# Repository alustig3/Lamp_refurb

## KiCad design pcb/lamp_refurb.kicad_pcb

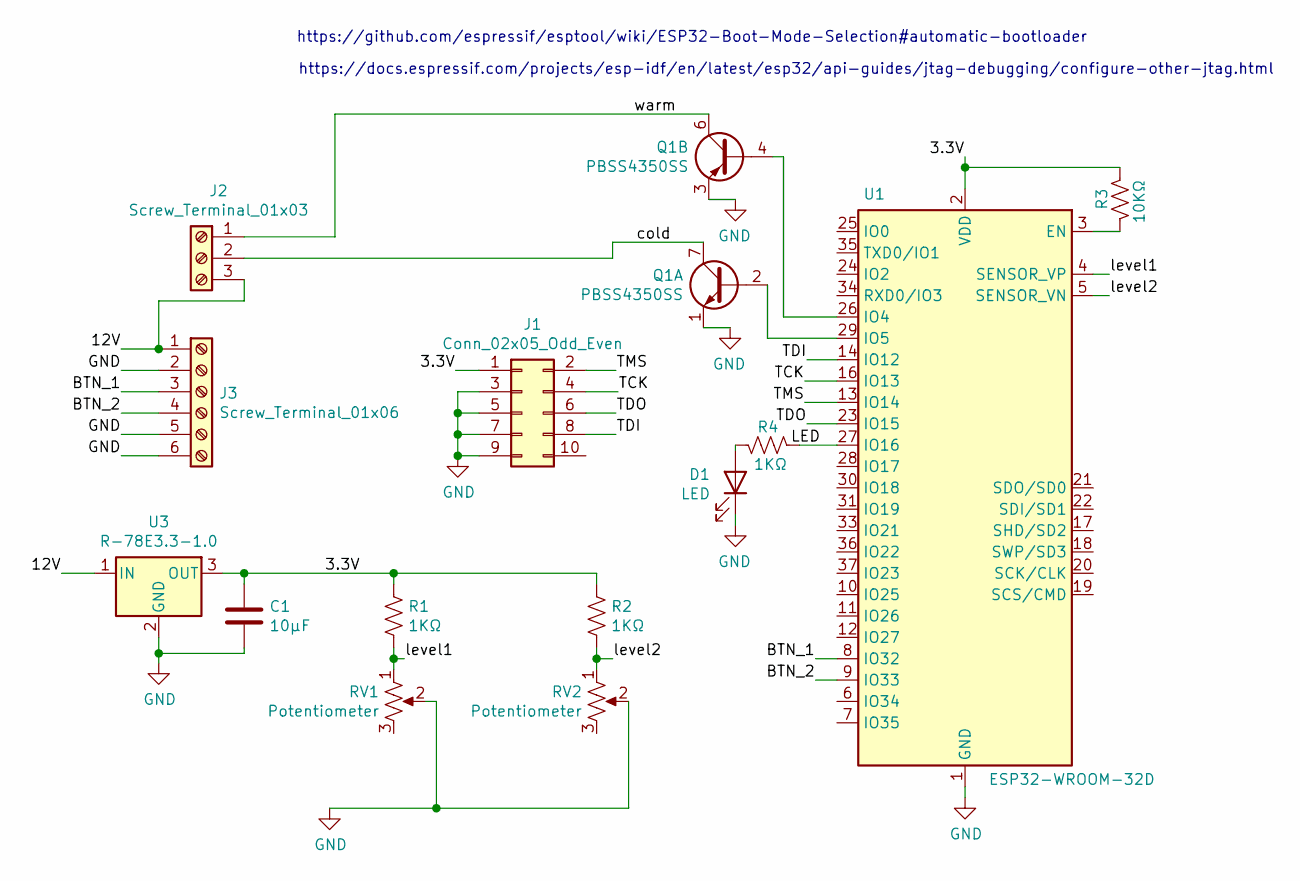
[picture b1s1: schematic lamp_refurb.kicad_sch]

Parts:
C1: 10µF; C_0805_2012Metric
D1: LED; LED_0805_2012Metric
J1: Conn_02x05_Odd_Even; SWD_2x5_socket
J2: Screw_Terminal_01x03; PinHeader_1x03_P2.54mm_Vertical
J3: Screw_Terminal_01x06; PinHeader_1x06_P2.54mm_Vertical
Q1: PBSS4350SS; SOIC-8_3.9x4.9mm_P1.27mm
R1, R2, R4: 1KΩ; R_0805_2012Metric
R3: 10KΩ; R_0805_2012Metric
RV1, RV2: Potentiometer; Panel_mount_pot
U1: ESP32-WROOM-32D; ESP32-WROOM-32
U3: R-78E3.3-1.0; Converter_DCDC_RECOM_R-78E-0.5_THT

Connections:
/3.3V: C1.1, J1.1, R1.1, R2.1, R3.2, U1.2 (VDD), U3.3 (OUT)
/12V: J2.3, J3.1, U3.1 (IN)
/BTN_1: J3.3, U1.8 (IO32)
/BTN_2: J3.4, U1.9 (IO33)
/LED: R4.2, U1.27 (IO16)
/TCK: J1.4, U1.16 (IO13)
/TDI: J1.8, U1.14 (IO12)
/TDO: J1.6, U1.23 (IO15)
/TMS: J1.2, U1.13 (IO14)
/cold: J2.2, Q1.7 (C1)
/level1: R1.2, RV1.1, U1.4 (SENSOR_VP)
/level2: R2.2, RV2.1, U1.5 (SENSOR_VN)
/warm: J2.1, Q1.6 (C2)
GND: C1.2, D1.1 (K), J1.3, J1.5, J1.7, J1.9, J3.2, J3.5, J3.6, Q1.1 (E1), Q1.3 (E2), RV1.2, RV2.2, U1.1 (GND), U1.15 (GND), U1.38 (GND), U1.39 (GND), U3.2 (GND)
unnamed: D1.2 (A), R4.1
unnamed: Q1.2 (B1), U1.29 (IO5)
unnamed: Q1.4 (B2), U1.26 (IO4)
unnamed: R3.1, U1.3 (EN)

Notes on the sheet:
https://github.com/espressif/esptool/wiki/ESP32-Boot-Mode-Selection#automatic-bootloader
https://docs.espressif.com/projects/esp-idf/en/latest/esp32/api-guides/jtag-debugging/configure-other-jtag.html

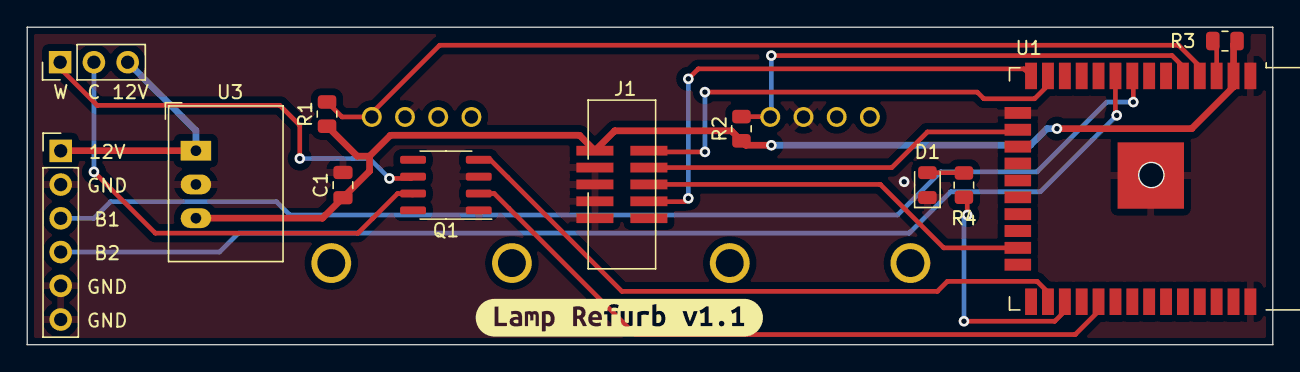
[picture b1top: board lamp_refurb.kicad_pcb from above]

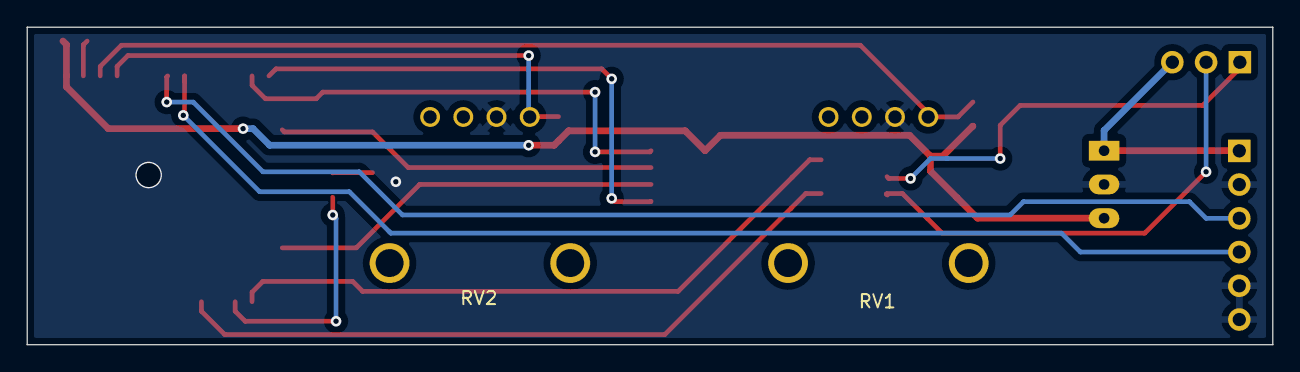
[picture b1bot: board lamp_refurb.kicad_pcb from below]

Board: 2 copper layers, 93.8 x 23.9 mm, 15 parts (2 on the bottom side), 18 nets.

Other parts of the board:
svg2mod: G***; svg2mod

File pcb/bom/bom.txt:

"Qty","Reference","Description","Value/MPN","Purchase Link"
"1","C1","0805 Capacitor","10µF","~"
"1","D1","","LED","~"
"1","J1","","Conn_02x05_Odd_Even","~"
"1","J2","","Screw_Terminal_01x03","~"
"1","J3","","Screw_Terminal_01x06","~"
"1","Q1","","PBSS4350SS","https://www.digikey.com/en/products/detail/nexperia-usa-inc/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"
"3","R1, R2, R4","0805 Resistor","1KΩ","~"
"1","R3","0805 Resistor","10KΩ","~"
"2","RV1, RV2","","Potentiometer","https://www.digikey.com/en/products/detail/bourns-inc/PTV111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"
"1","U1","","ESP32-WROOM-32D","https://www.espressif.com/sites/default/files/documentation/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"
"1","U3","","R-78E3.3-1.0","https://www.digikey.com/en/products/detail/recom-power/R-78E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"

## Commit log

2020-10-12 PCB v1.0
2020-10-22 working software
2020-10-23 Updates output only when there is change in input
2020-10-26 Red btn features
    - now only tries to handle events if put into update mode by holding red button while light is off
    - holding red button while light is on, turns LEDs on full blast
2020-10-26 changed interface
    - pressing black button puts it in high power mode
    - otherwise, inner knob is color and outer knob is brightness
2020-11-24 cleaned up code
2020-11-24 telegram notifications working
2020-12-01 Lamp on duration send to telegram
2020-12-31 trying to debug
    after about a week, messages stop being sent. want to see if the MCU is getting an error when sending message to telegram, or if it thinks everything is working.
2021-01-18 fixed connection issue
    - if wifi connection was ever lost, messages from telegram would stop being succesful
    - added function for reconnecting wifi if received error from telegram message attempt
2021-02-22 removed wifi features
2021-04-26 PCB v1.1
2021-04-26 moved files
